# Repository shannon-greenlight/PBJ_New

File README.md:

# PBJ_New
# This project has been replaced by PBJ_EU_3.

PBJ Project (Proto Board with Jacks) -- For Synthesizer hardware development

https://www.greenfacelabs.com/pbj-eu/

This project provides the KiCAD files used to fab PBJ synthesizer development breadboards.
It requires the KiCAD libraries found at: https://github.com/shannon-greenlight/KiCAD

It also requires the Digi-Key footprint and symbol libraries available at: https://www.digikey.com/en/resources/design-tools/kicad

Add these paths to the symbol libraries:

dk_Sockets-for-ICs-Transistors	.../KiCAD/digikey-symbols/dk_Sockets-for-ICs-Transistors.lib		

dk_Rectangular-Connectors-Headers-Male-Pins	.../KiCAD/digikey-symbols/dk_Rectangular-Connectors-Headers-Male-Pins.lib		

dk_Pushbutton-Switches	.../KiCAD/digikey-symbols/dk_Pushbutton-Switches.lib

greenface-symbols	...\KiCAD\greenface-symbols.lib		

Add these paths to the footprint libraries:

digikey-footprints	.../KiCAD/digikey-footprints.pretty		

panel	...\KiCAD\panel.pretty		

sputterizer	...\KiCAD\sputterizer.pretty		

The Excel file pbj_eu.xlsx can be uploaded directly to Digi-Key to order parts.

Currently, only the PBJ EU is available. But a standalone version, the PBJ Solo, is in the wings.

Note: If you don't have KiCAD and just want to make the PBJ, you can send the Gerber files to fab and use the Excel file to buy the parts. 
The jpegs of the EU in use (EU_inuse.jpg) and of the schematic (PBJ_EU/pbj_eu.jpg) can be used for reference.

PBJ EU Features

800 point solderless proto board

4 switched 3.5mm jacks

Wiring connector interfaces jacks and power to proto board

LED monitors for each jack. Red indicates positive voltage present. Blue indicates negative.

Test point per jack gives convenient access for scope/meter probes.

2 Large Ground connection points are excellent for attaching alligator clips

2 MULT switches connect jack 1 to 2 or jack 3 to 4.

Tip and Switch signals are routed from the jacks to the wiring connector.

+/- 12V and +5V power are routed to the wiring connector.

Power is switched.

Power indicator shows presence of +5V.

10 pin EU power output connector can be used to power off-rack modules.

22 HP wide

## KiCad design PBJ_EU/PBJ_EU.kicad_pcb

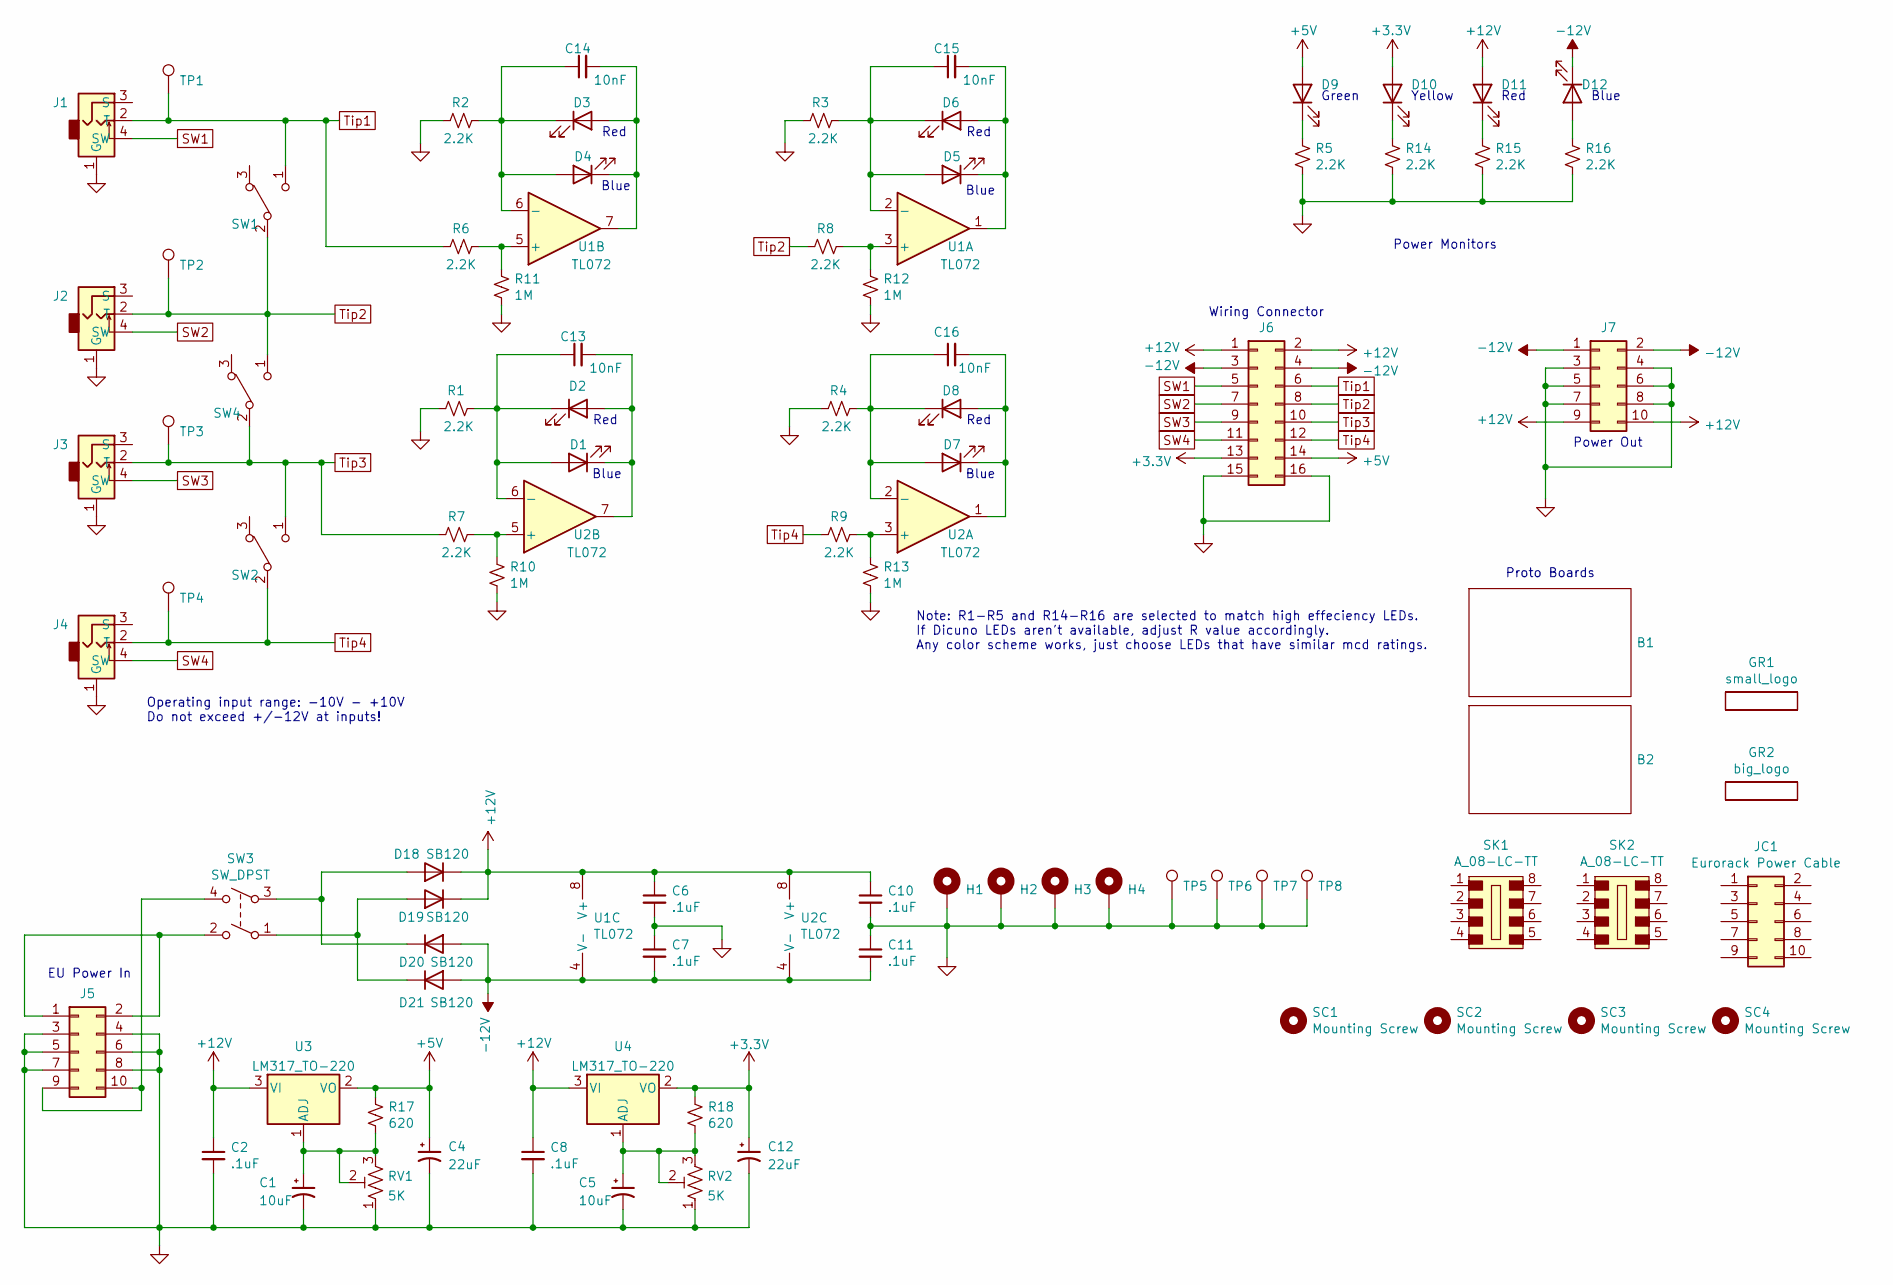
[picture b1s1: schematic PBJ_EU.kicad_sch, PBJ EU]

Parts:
B1, B2: Breadboard_400; Proto_400; Digi-Key Part 1286-1185-ND
C1, C5: 10uF; CP_Radial_D5.0mm_P2.00mm; Digi-Key Part P124234CT-ND
C2, C6, C7, C8, C10, C11: .1uF; C_Rect_L7.0mm_W2.0mm_P5.00mm; Digi-Key Part 478-3188-ND
C4, C12: 22uF; CP_Radial_D5.0mm_P2.00mm; Digi-Key Part P15374CT-ND
C13, C14, C15, C16: 10nF; C_Rect_L7.0mm_W2.0mm_P5.00mm; Digi-Key Part BC2662CT-ND
D1, D4, D5, D7, D12: BLUE LED; LED_D3.0mm
D2, D3, D6, D8, D11: RED LED; LED_D3.0mm
D9: GREEN LED; LED_D3.0mm
D10: YELLOW LED; LED_D3.0mm
D18, D19, D20, D21: SB120; D_DO-41_SOD81_P7.62mm_Horizontal; Digi-Key Part 112-SB120-E3/54CT-ND
GR1: small_logo; small_face
GR2: big_logo; logo_black
H1, H2, H3, H4: MountingHole_Pad; MountingHole_3.2mm_M3_SmPad
J1, J2, J3, J4: Molex_47257; Molex-0472570001; Digi-Key Part WM17366-ND
J5, J7: Conn_02x05_Odd_Even; PinHeader_2x05_P2.54mm_Vertical; Digi-Key Part S2011EC-05-ND
J6: Conn_02x08_Odd_Even_Female; PinHeader_2x08_P2.54mm_Vertical; Digi-Key Part S7111-ND
JC1: Eurorack Power Cable; Digi-Key Part H3CCS-1018G-ND
R1, R2, R3, R4, R5, R6, R7, R8, R9, R14, R15, R16: 2.2K; R_Axial_DIN0207_L6.3mm_D2.5mm_P10.16mm_Horizontal; Digi-Key Part CF14JT2K20CT-ND
R10, R11, R12, R13: 1M; R_Axial_DIN0207_L6.3mm_D2.5mm_P10.16mm_Horizontal; Digi-Key Part CF14JT1M00CT-ND
R17, R18: 620; R_Axial_DIN0207_L6.3mm_D2.5mm_P10.16mm_Horizontal; Digi-Key Part S620CACT-ND
RV1, RV2: 5K; Potentiometer_Bourns_3296W_Vertical; Digi-Key Part 3296W-502LF-ND
SC1, SC2, SC3, SC4: Mounting Screw; Digi-Key Part 335-1156-ND
SK1, SK2: A_08-LC-TT; DIP-8_W7.62mm_Socket_LongPads; Digi-Key Part AE9986-ND
SW1, SW2, SW4: SW_SPDT; SW_Slide_1P2T_CK_OS102011MS2Q; Digi-Key Part CKN10397-ND
SW3: SW_DPST; S202031MS02Q; Digi-Key Part CKN9891-ND
TP1, TP2, TP3, TP4: TestPoint; TestPoint_Keystone_5005-5009_Compact; Digi-Key Part 36-5006-ND
TP5, TP6, TP7, TP8: TestPoint; TestPoint_Keystone_5005-5009_Compact
U1, U2: TL072; DIP-8_W7.62mm_Socket_LongPads; Digi-Key Part 296-1775-5-ND
U3, U4: LM317_TO-220; TO-220-3_Vertical; Digi-Key Part 497-19621-ND

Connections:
+3V3: C12.1, D10.2 (A), J6.13, R18.1, U4.2 (VO)
+5V: C4.1, D9.2 (A), J6.14, R17.1, U3.2 (VO)
+12V: C2.1, C6.1, C8.1, C10.1, D11.2 (A), D18.1 (K), D19.1 (K), J6.1, J6.2, J7.9, J7.10, U1.8 (V+), U2.8 (V+), U3.3 (VI), U4.3 (VI)
-12V: C7.2, C11.2, D12.1 (K), D20.2 (A), D21.2 (A), J6.3, J6.4, J7.1, J7.2, U1.4 (V-), U2.4 (V-)
GND: C1.2, C2.2, C4.2, C5.2, C6.2, C7.1, C8.2, C10.2, C11.1, C12.2, H1.1, H2.1, H3.1, H4.1, J1.1 (G), J2.1 (G), J3.1 (G), J4.1 (G), J5.3, J5.4, J5.5, J5.6, J5.7, J5.8, J6.15, J6.16, J7.3, J7.4, J7.5, J7.6, J7.7, J7.8, R1.1, R2.1, R3.1, R4.1, R5.2, R10.2, R11.2, R12.2, R13.2, R14.2, R15.2, R16.2, RV1.1, RV2.1, TP5.1, TP6.1, TP7.1, TP8.1
unnamed: C1.1, R17.2, RV1.2, RV1.3, U3.1 (ADJ)
unnamed: C5.1, R18.2, RV2.2, RV2.3, U4.1 (ADJ)
unnamed: C13.1, D1.2 (A), D2.1 (K), R1.2, U2.6 (-)
unnamed: C13.2, D1.1 (K), D2.2 (A), U2.7
unnamed: C14.1, D3.1 (K), D4.2 (A), R2.2, U1.6 (-)
unnamed: C14.2, D3.2 (A), D4.1 (K), U1.7
unnamed: C15.1, D5.2 (A), D6.1 (K), R3.2, U1.2 (-)
unnamed: C15.2, D5.1 (K), D6.2 (A), U1.1
unnamed: C16.1, D7.2 (A), D8.1 (K), R4.2, U2.2 (-)
unnamed: C16.2, D7.1 (K), D8.2 (A), U2.1
unnamed: D9.1 (K), R5.1
unnamed: D10.1 (K), R14.1
unnamed: D11.1 (K), R15.1
unnamed: D12.2 (A), R16.1
unnamed: D18.2 (A), D20.1 (K), SW3.3
unnamed: D19.2 (A), D21.1 (K), SW3.1
unnamed: J5.1, J5.2, SW3.2
unnamed: J5.9, J5.10, SW3.4
unnamed: R7.1, R10.1, U2.5 (+)
unnamed: R6.1, R11.1, U1.5 (+)
unnamed: R8.1, R12.1, U1.3 (+)
unnamed: R9.1, R13.1, U2.3 (+)
SW1: J1.4 (SW), J6.5
SW2: J2.4 (SW), J6.7
SW3: J3.4 (SW), J6.9
SW4: J4.4 (SW), J6.11
Tip1: J1.2 (T), J6.6, R6.2, SW1.1 (A), TP1.1
Tip2: J2.2 (T), J6.8, R8.2, SW1.2 (B), SW4.1 (A), TP2.1
Tip3: J3.2 (T), J6.10, R7.2, SW2.1 (A), SW4.2 (B), TP3.1
Tip4: J4.2 (T), J6.12, R9.2, SW2.2 (B), TP4.1

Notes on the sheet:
EU Power In
Blue
Proto Boards
Red
Wiring Connector
Yellow
Power Monitors
Operating input range: -10V - +10V Do not exceed +/-12V at inputs!
Note: R1-R5 and R14-R16 are selected to match high effeciency LEDs. If Dicuno LEDs aren't available, adjust R value accordingly. Any color scheme works, just choose LEDs that have similar mcd ratings.
Power Out
Green

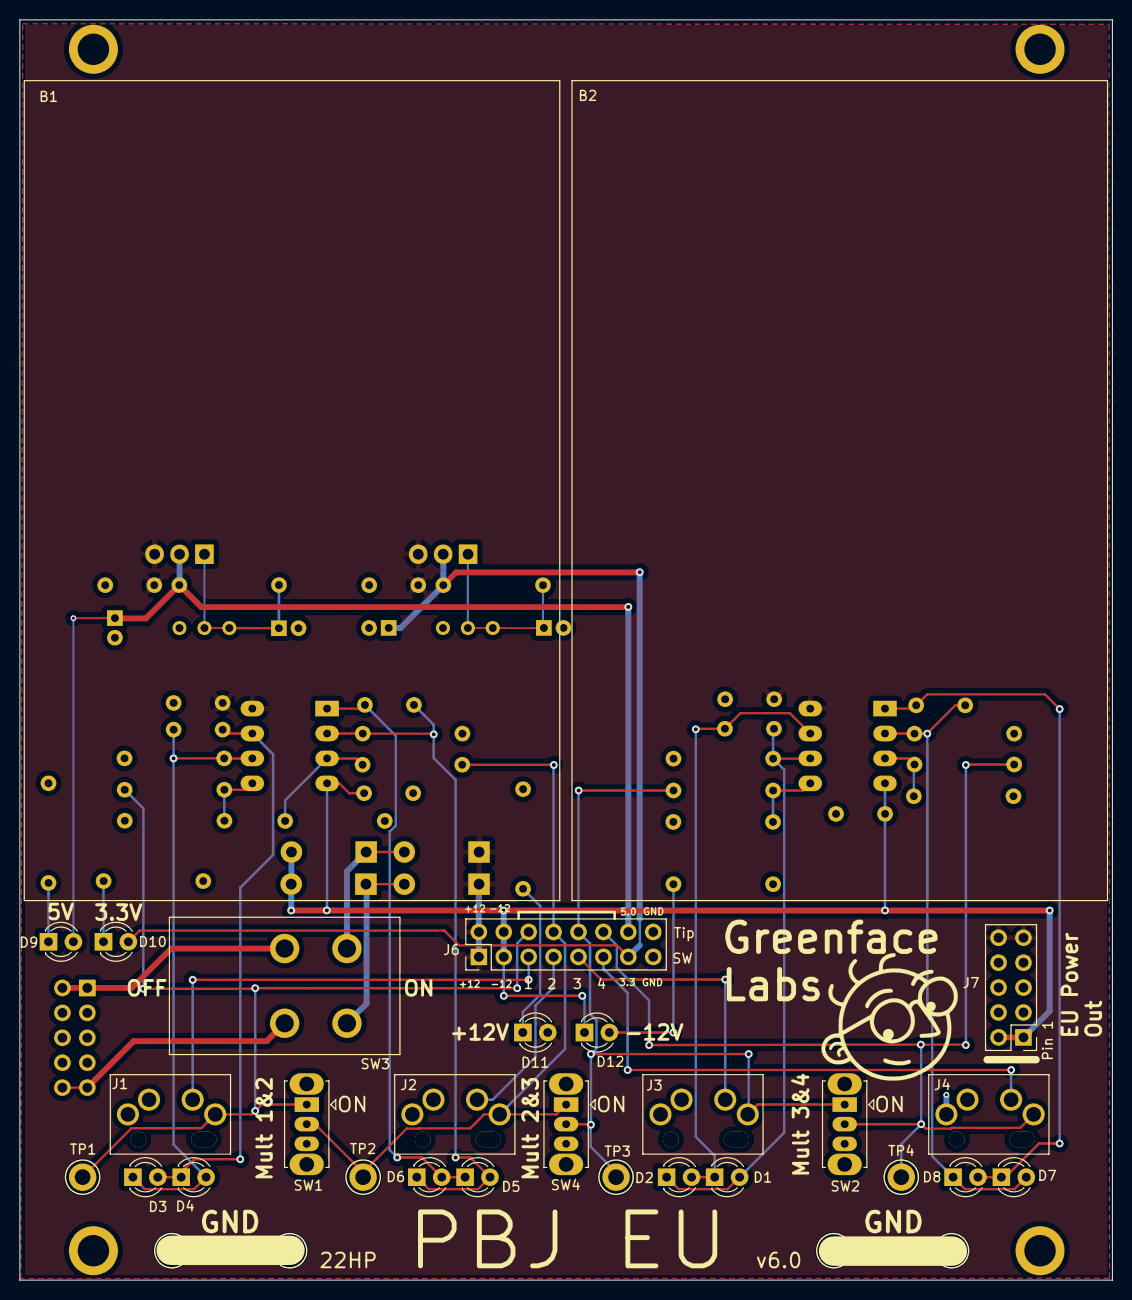
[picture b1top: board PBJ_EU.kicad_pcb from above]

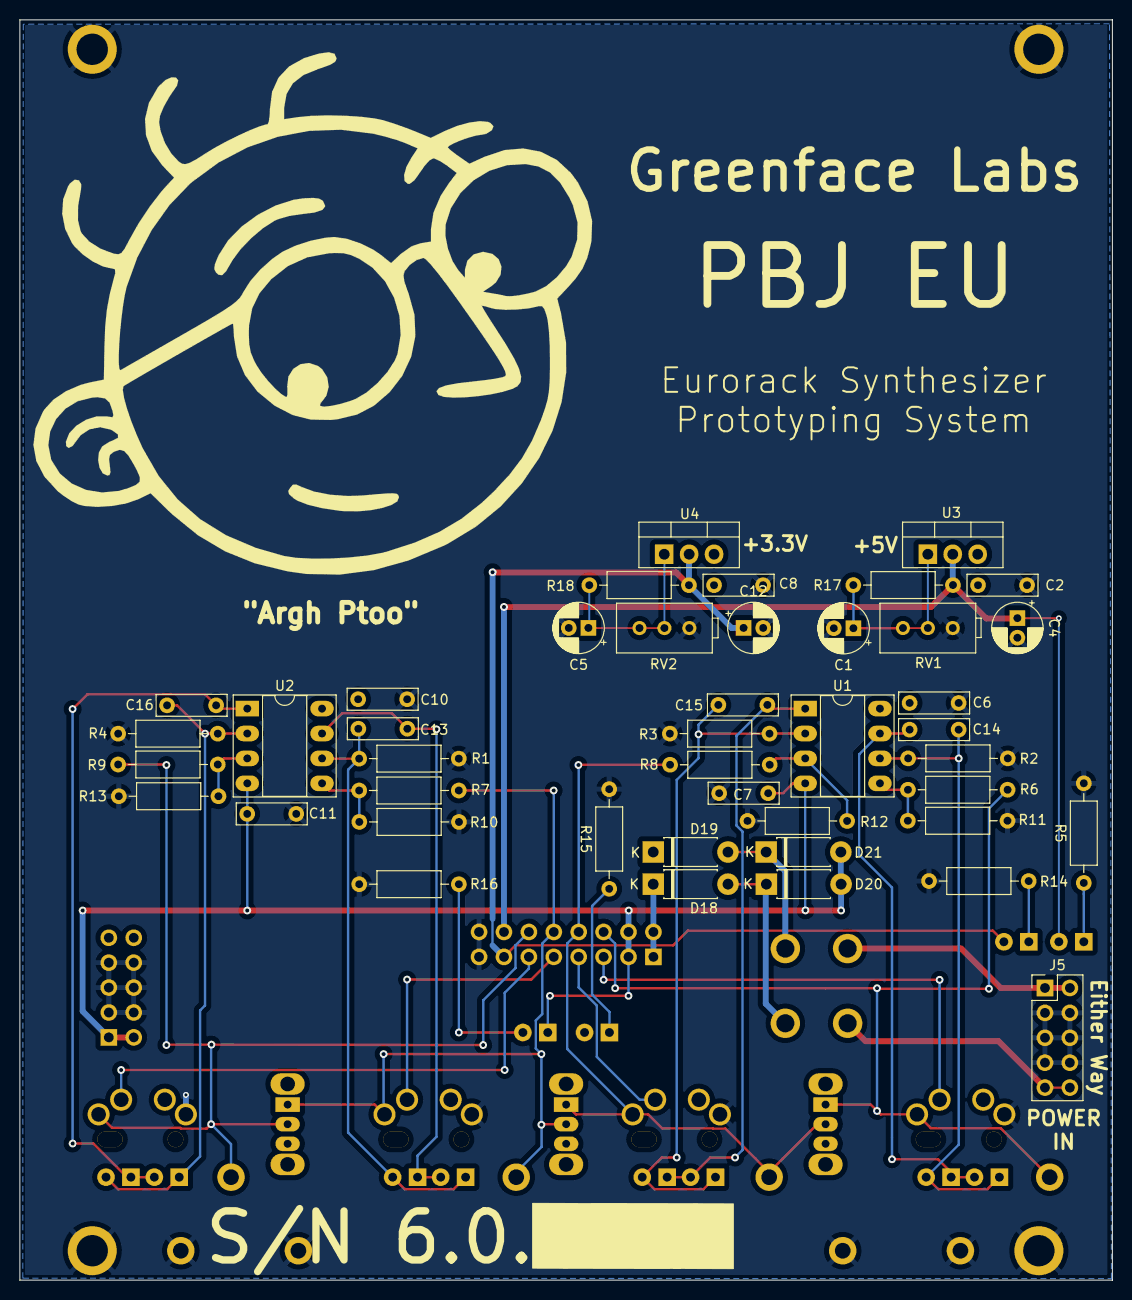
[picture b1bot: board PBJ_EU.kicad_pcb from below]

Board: 2 copper layers, 111.4 x 128.5 mm, 81 parts (44 on the bottom side), 35 nets.

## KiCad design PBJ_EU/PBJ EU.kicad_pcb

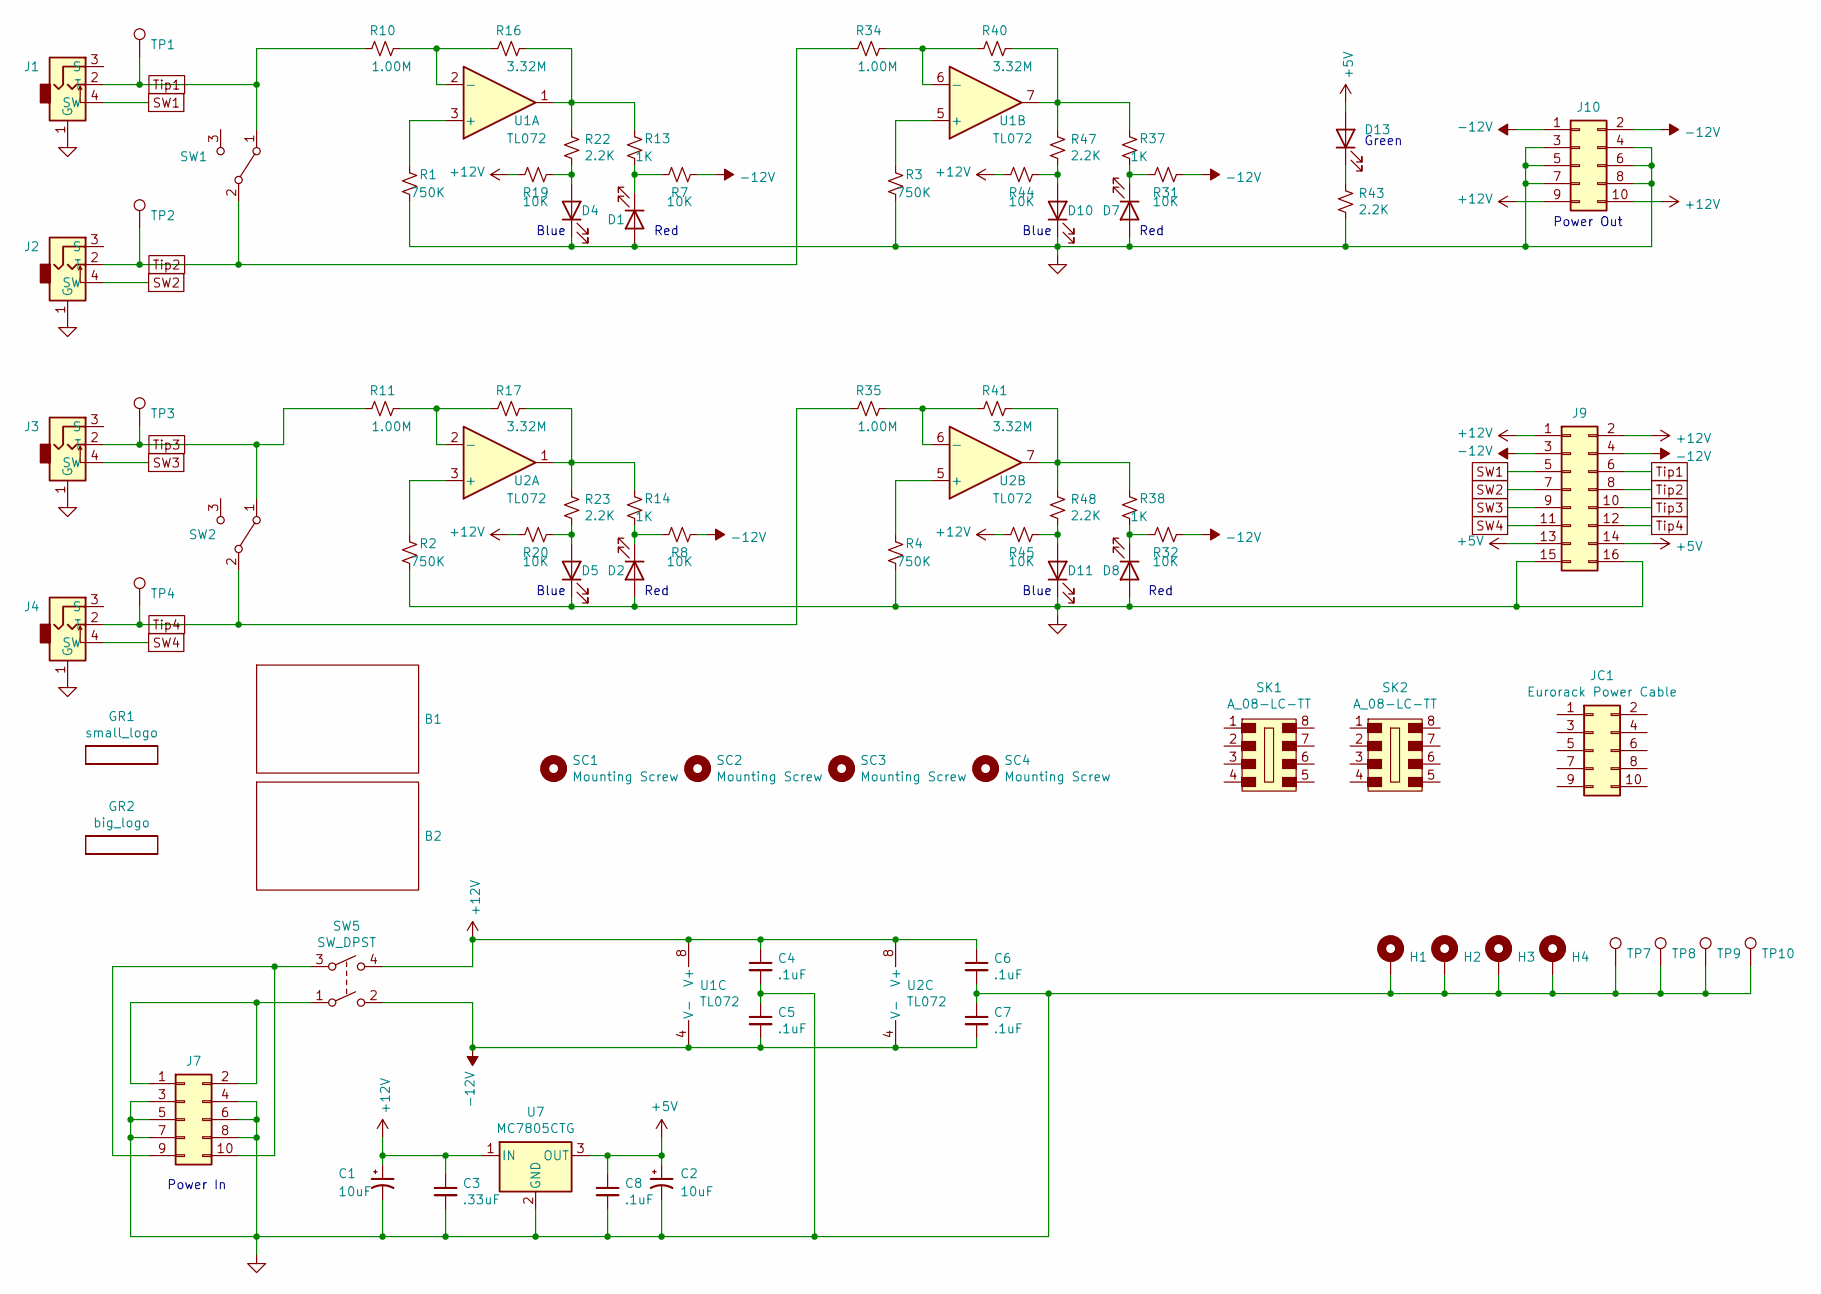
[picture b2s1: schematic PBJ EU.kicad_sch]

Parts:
B1, B2: Breadboard_400; Proto_400; Digi-Key Part 1286-1185-ND
C1, C2: 10uF; CP_Radial_Tantal_D5.0mm_P5.00mm; Digi-Key Part 478-7366-1-ND
C3: .33uF; C_Rect_L7.0mm_W2.0mm_P5.00mm; Digi-Key Part 445-180638-1-ND
C4, C5, C6, C7, C8: .1uF; C_Rect_L7.0mm_W2.0mm_P5.00mm; Digi-Key Part 478-3188-ND
D1, D2, D7, D8: RED LED; LED_D3.0mm; Digi-Key Part 732-5005-ND
D4, D5, D10, D11: BLUE LED; LED_D3.0mm; Digi-Key Part 732-11401-ND
D13: GREEN LED; LED_D3.0mm; Digi-Key Part 732-5008-ND
GR1: small_logo; small_face
GR2: big_logo; logo_black
H1, H2, H3, H4: MountingHole_Pad; MountingHole_3.2mm_M3_SmPad
J1, J2, J3, J4: Molex_47257; Molex-0472570001; Digi-Key Part WM17366-ND
J7, J10: Conn_02x05_Odd_Even; PinHeader_2x05_P2.54mm_Vertical; Digi-Key Part S2011EC-05-ND
J9: Conn_02x08_Odd_Even_Female; PinHeader_2x08_P2.54mm_Vertical; Digi-Key Part S7111-ND
JC1: Eurorack Power Cable; Digi-Key Part H3CCS-1018G-ND
R1, R2, R3, R4: 750K; R_Axial_DIN0207_L6.3mm_D2.5mm_P10.16mm_Horizontal; Digi-Key Part S750KQCT-ND
R7, R8, R19, R20, R31, R32, R44, R45: 10K; R_Axial_DIN0207_L6.3mm_D2.5mm_P10.16mm_Horizontal; Digi-Key Part CF14JT10K0CT-ND
R10, R11, R34, R35: 1.00M; R_Axial_DIN0207_L6.3mm_D2.5mm_P10.16mm_Horizontal; Digi-Key Part RNF14FTD1M00CT-ND
R13, R14, R37, R38: 1K; R_Axial_DIN0207_L6.3mm_D2.5mm_P10.16mm_Horizontal; Digi-Key Part CF14JT1K00CT-ND
R16, R17, R40, R41: 3.32M; R_Axial_DIN0207_L6.3mm_D2.5mm_P10.16mm_Horizontal; Digi-Key Part RNF14FTD3M32CT-ND
R22, R23, R43, R47, R48: 2.2K; R_Axial_DIN0207_L6.3mm_D2.5mm_P10.16mm_Horizontal; Digi-Key Part CF14JT2K20CT-ND
SC1, SC2, SC3, SC4: Mounting Screw; Digi-Key Part 335-1156-ND
SK1, SK2: A_08-LC-TT; Digi-Key Part AE9986-ND
SW1, SW2: SW_SPDT; SW_Slide_1P2T_CK_OS102011MS2Q; Digi-Key Part CKN10397-ND
SW5: SW_DPST; S202031MS02Q; Digi-Key Part CKN9891-ND
TP1, TP2, TP3, TP4, TP7, TP8, TP9, TP10: TestPoint; TestPoint_Keystone_5005-5009_Compact; Digi-Key Part 36-5006-ND
U1: TL072
U2: TL072; DIP-8_W7.62mm; Digi-Key Part 296-14997-5-ND‎
U7: MC7805CTG; TO-220-3_Vertical; Digi-Key Part MC7805CTGOS-ND

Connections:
+5V: C2.1, C8.1, D13.2 (A), J9.13, J9.14, U7.3 (OUT)
+12V: C1.1, C3.1, C4.1, C6.1, J9.1, J9.2, J10.9, J10.10, R19.1, R20.1, R44.1, R45.1, SW5.4, U1.8 (V+), U2.8 (V+), U7.1 (IN)
-12V: C5.2, C7.2, J9.3, J9.4, J10.1, J10.2, R7.2, R8.2, R31.2, R32.2, SW5.2, U1.4 (V-), U2.4 (V-)
GND: C1.2, C2.2, C3.2, C4.2, C5.1, C6.2, C7.1, C8.2, D1.2 (A), D2.2 (A), D4.1 (K), D5.1 (K), D7.2 (A), D8.2 (A), D10.1 (K), D11.1 (K), H1.1, H2.1, H3.1, H4.1, J1.1 (G), J2.1 (G), J3.1 (G), J4.1 (G), J7.3, J7.4, J7.5, J7.6, J7.7, J7.8, J9.15, J9.16, J10.3, J10.4, J10.5, J10.6, J10.7, J10.8, R1.2, R2.2, R3.2, R4.2, R43.2, TP7.1, TP8.1, TP9.1, TP10.1, U7.2 (GND)
unnamed: D1.1 (K), R7.1, R13.2
unnamed: D2.1 (K), R8.1, R14.2
unnamed: D4.2 (A), R19.2, R22.2
unnamed: D5.2 (A), R20.2, R23.2
unnamed: D7.1 (K), R31.1, R37.2
unnamed: D8.1 (K), R32.1, R38.2
unnamed: D10.2 (A), R44.2, R47.2
unnamed: D11.2 (A), R45.2, R48.2
unnamed: D13.1 (K), R43.1
unnamed: J7.1, J7.2, SW5.1
unnamed: J7.9, J7.10, SW5.3
unnamed: R1.1, U1.3 (+)
unnamed: R2.1, U2.3 (+)
unnamed: R3.1, U1.5 (+)
unnamed: R4.1, U2.5 (+)
unnamed: R10.2, R16.1, U1.2 (-)
unnamed: R11.2, R17.1, U2.2 (-)
unnamed: R13.1, R16.2, R22.1, U1.1
unnamed: R14.1, R17.2, R23.1, U2.1
unnamed: R34.2, R40.1, U1.6 (-)
unnamed: R35.2, R41.1, U2.6 (-)
unnamed: R37.1, R40.2, R47.1, U1.7
unnamed: R38.1, R41.2, R48.1, U2.7
SW1: J1.4 (SW), J9.5
SW2: J2.4 (SW), J9.7
SW3: J3.4 (SW), J9.9
SW4: J4.4 (SW), J9.11
Tip1: J1.2 (T), J9.6, R10.1, SW1.1 (A), TP1.1
Tip2: J2.2 (T), J9.8, R34.1, SW1.2 (B), TP2.1
Tip3: J3.2 (T), J9.10, R11.1, SW2.1 (A), TP3.1
Tip4: J4.2 (T), J9.12, R35.1, SW2.2 (B), TP4.1

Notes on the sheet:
Blue
Power In
Red
Power Out
Green

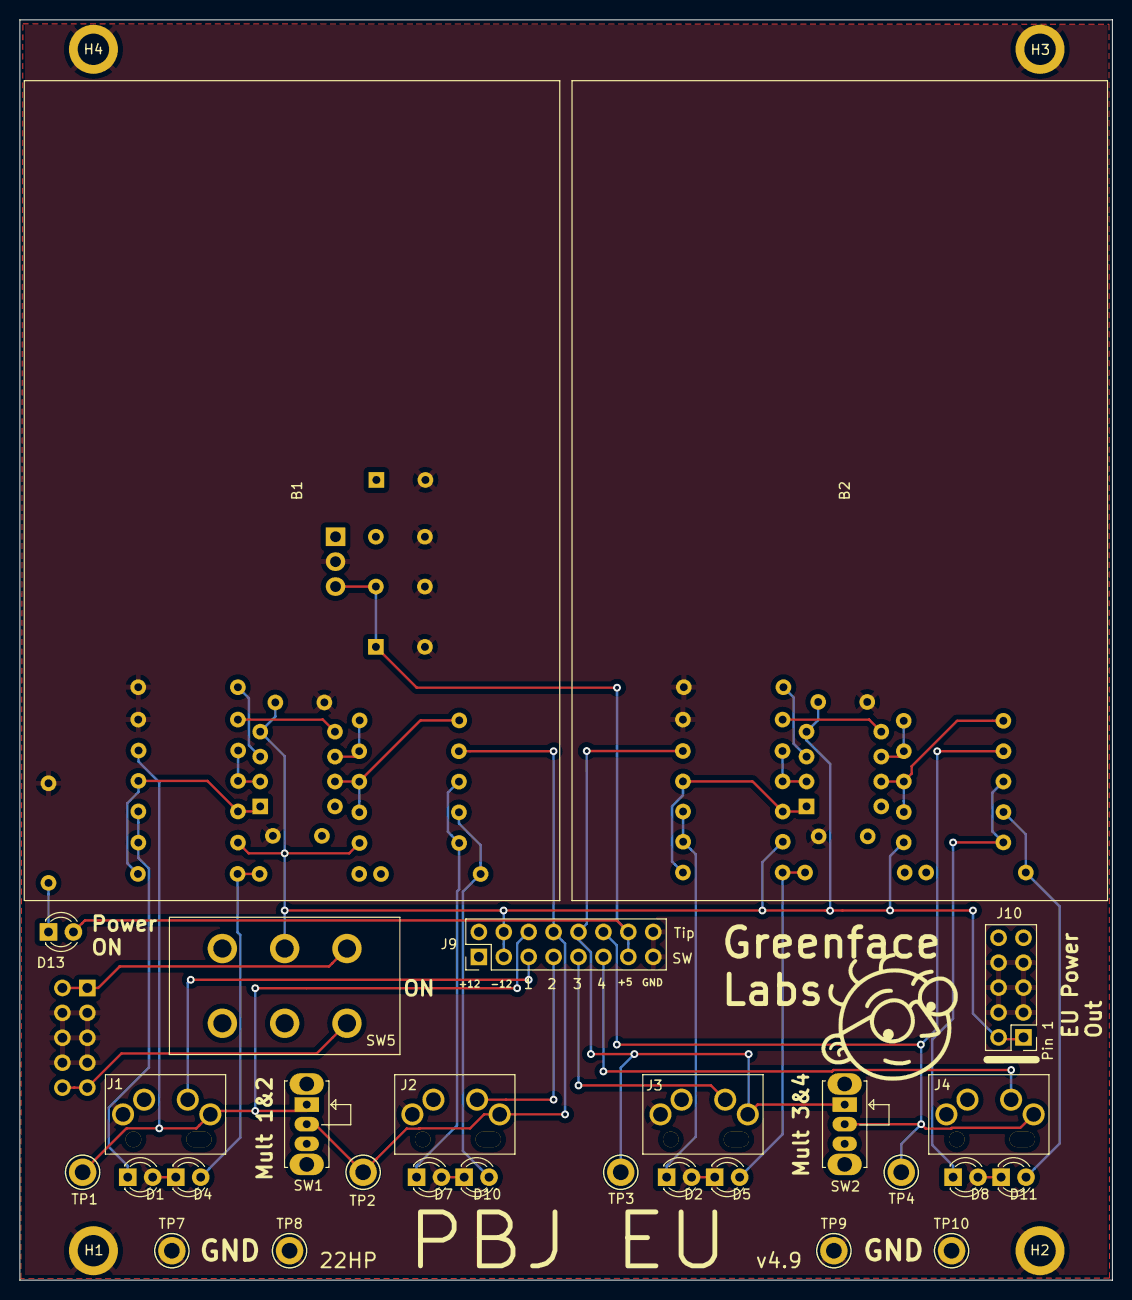
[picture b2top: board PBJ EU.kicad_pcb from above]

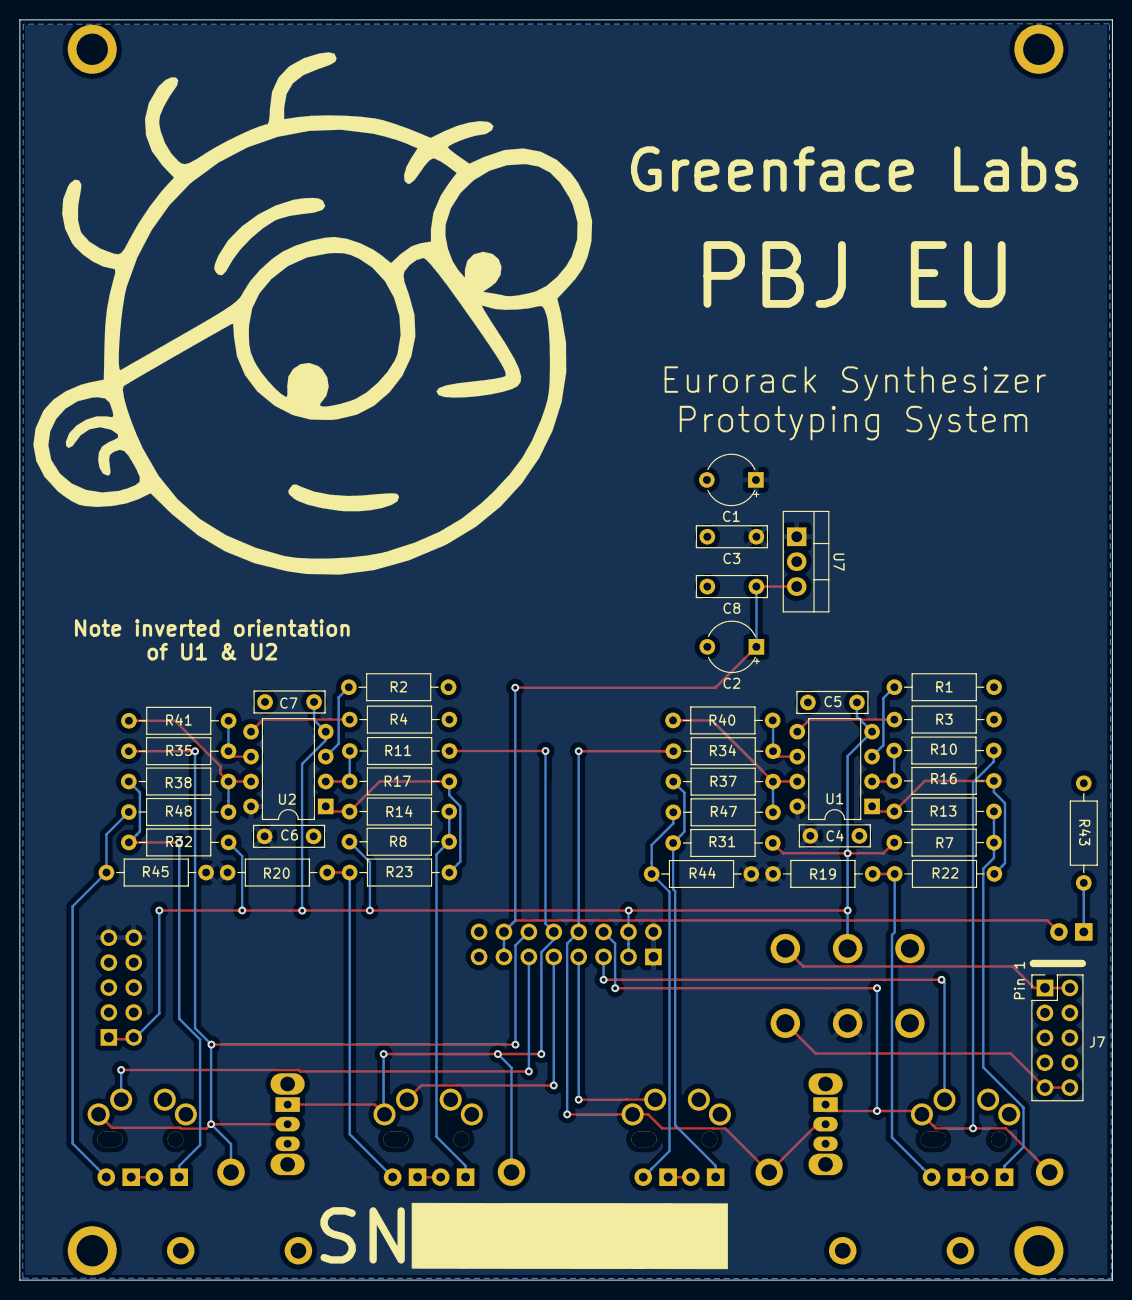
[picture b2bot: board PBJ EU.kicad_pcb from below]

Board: 2 copper layers, 111.4 x 128.5 mm, 75 parts (42 on the bottom side), 35 nets.

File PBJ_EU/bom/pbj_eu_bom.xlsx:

Reference | Quantity | Value | Digi-Key Part
B1 B2 | 2 | Breadboard_400 | 1286-1185-ND
C1 C2 | 2 | 10uF | 478-7366-1-ND
C4 C5 C6 C7 | 4 | .1uF | 478-3188-ND
D13 | 1 | GREEN LED | 732-5008-ND
D2 D8 D1 D7 | 4 | RED LED | 732-5005-ND
D5 D11 D4 D10 | 4 | BLUE LED | 732-11401-ND
J1 J2 J3 J4 | 4 | Molex_47257-spankulator-rescue | WM17366-ND
J7 J10 | 2 | Conn_02x05_Odd_Even | S2011EC-05-ND
J9 | 1 | Conn_02x08_Odd_Even_Female | S7111-ND
R10 R34 R11 R35 | 4 | 1.00M | RNF14FTD1M00CT-ND
R14 R38 R13 R37 | 4 | 1K | CF14JT1K00CT-ND
R16 R40 R41 R17 | 4 | 3.32M | RNF14FTD3M32CT-ND
R20 R8 R45 R32 R19 R7 R44 R31 | 8 | 10K | CF14JT10K0CT-ND
R43 R23 R48 R22 R47 | 5 | 2.2K | CF14JT2K20CT-ND
SW1 SW2 | 2 | SW_SPDT | CKN10397-ND
SW5 | 1 | SW_DPST | CKN9891-ND
TP1 TP2 TP3 TP4 TP7 TP8 TP9 TP10 | 8 | TestPoint | 36-5006-ND
U1 U2 | 2 | TL072 | 296-14997-5-ND
U7 | 1 | MC7805CTG | MC7805CTGOS-ND
JC1 | 1 | Eurorack Power Cable | H3CCS-1618G-ND
SC1 SC2 SC3 SC4 | 4 | Mounting Screw | 335-1156-ND
SK1 SK2 | 2 | A_08-LC-TT | AE9986-ND

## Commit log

2020-11-12 Init checkin for ver 2.0
2020-12-08 ver 3.0
2021-01-26 Removed raw spice files
2021-01-26 Removed unused KiCAD files.
2021-01-26 Updates spice to match schematic values.
2021-12-25 Fixed rescue libs
2021-12-25 Adds jpeg of schematic
2021-12-25 Moves zip files
2021-12-25 A little formatting of excel file.
2021-12-25 Adds gerber files
2021-12-25 Updates to ver 4.7.
2021-12-25 Adds jpeg and updates readme
2022-01-27 version 4.8
    Fixes power connector.
2022-01-28 v 4.9
    Adds caps to regulator. Adds graphics and text.
2022-02-19 Move to KiCAD 6.0
2022-02-19 Fixed 3d models
    Some 3d models are still unavailable
2022-02-19 Changed name so that BOM would work
    Looks like 6.0 BOM bombs when there is a space in the filename.
2022-02-19 Adds BOM
2022-02-22 Updates footprint 3d shapes
2022-03-04 Adds pdf of schematic
2022-08-20 Version 4.10
2022-09-20 Adds note to schematic about 3.3V regulator option
2022-11-12 v5.2
    Adds LCSC build support. Fixes to monitor circuitry.
2022-11-12 Update PBJ_EU.kicad_sch
    Testing branch
2022-11-15 lm317 experiment checkin
2022-11-16 Uses LM317 for regulators now.
2024-04-23 add file to .gitignore
